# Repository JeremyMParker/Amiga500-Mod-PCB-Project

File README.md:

# Amiga500-Mod-PCB-Project
A small back panel PCB to house HDMI and several switches...
This small 4-layer PCB will take an HDMI mini cable from a Raspberry Pi RGB-to-HDMI and convert to normal size HDMI for plugging into the Amiga.
There is one small SPST push-button switch to allow menu access to the Raspberry Pi by way of a 2-pin 100mil spaced header.
A miniture DPDT switch is wired to a 4-pin 100mil header to allow the Amiga-Kit DF0/DF1 select switch cable to plug right in.
A miniture 3PDT switch is wired to a 4-pin 100mil header to allow access to the Amiga Audio Filter Mod as described in my YouTube video.
The Audio Filter control either lets the Amiga control the output low-pass filters, or overrides the Amiga and forces the filters to be enabled/disabled.
The PCB is just barely wide enough to fit in the blank space on the left side of the A500 when looking at the back.
This is my first GitHub repository, so please be patient with me!

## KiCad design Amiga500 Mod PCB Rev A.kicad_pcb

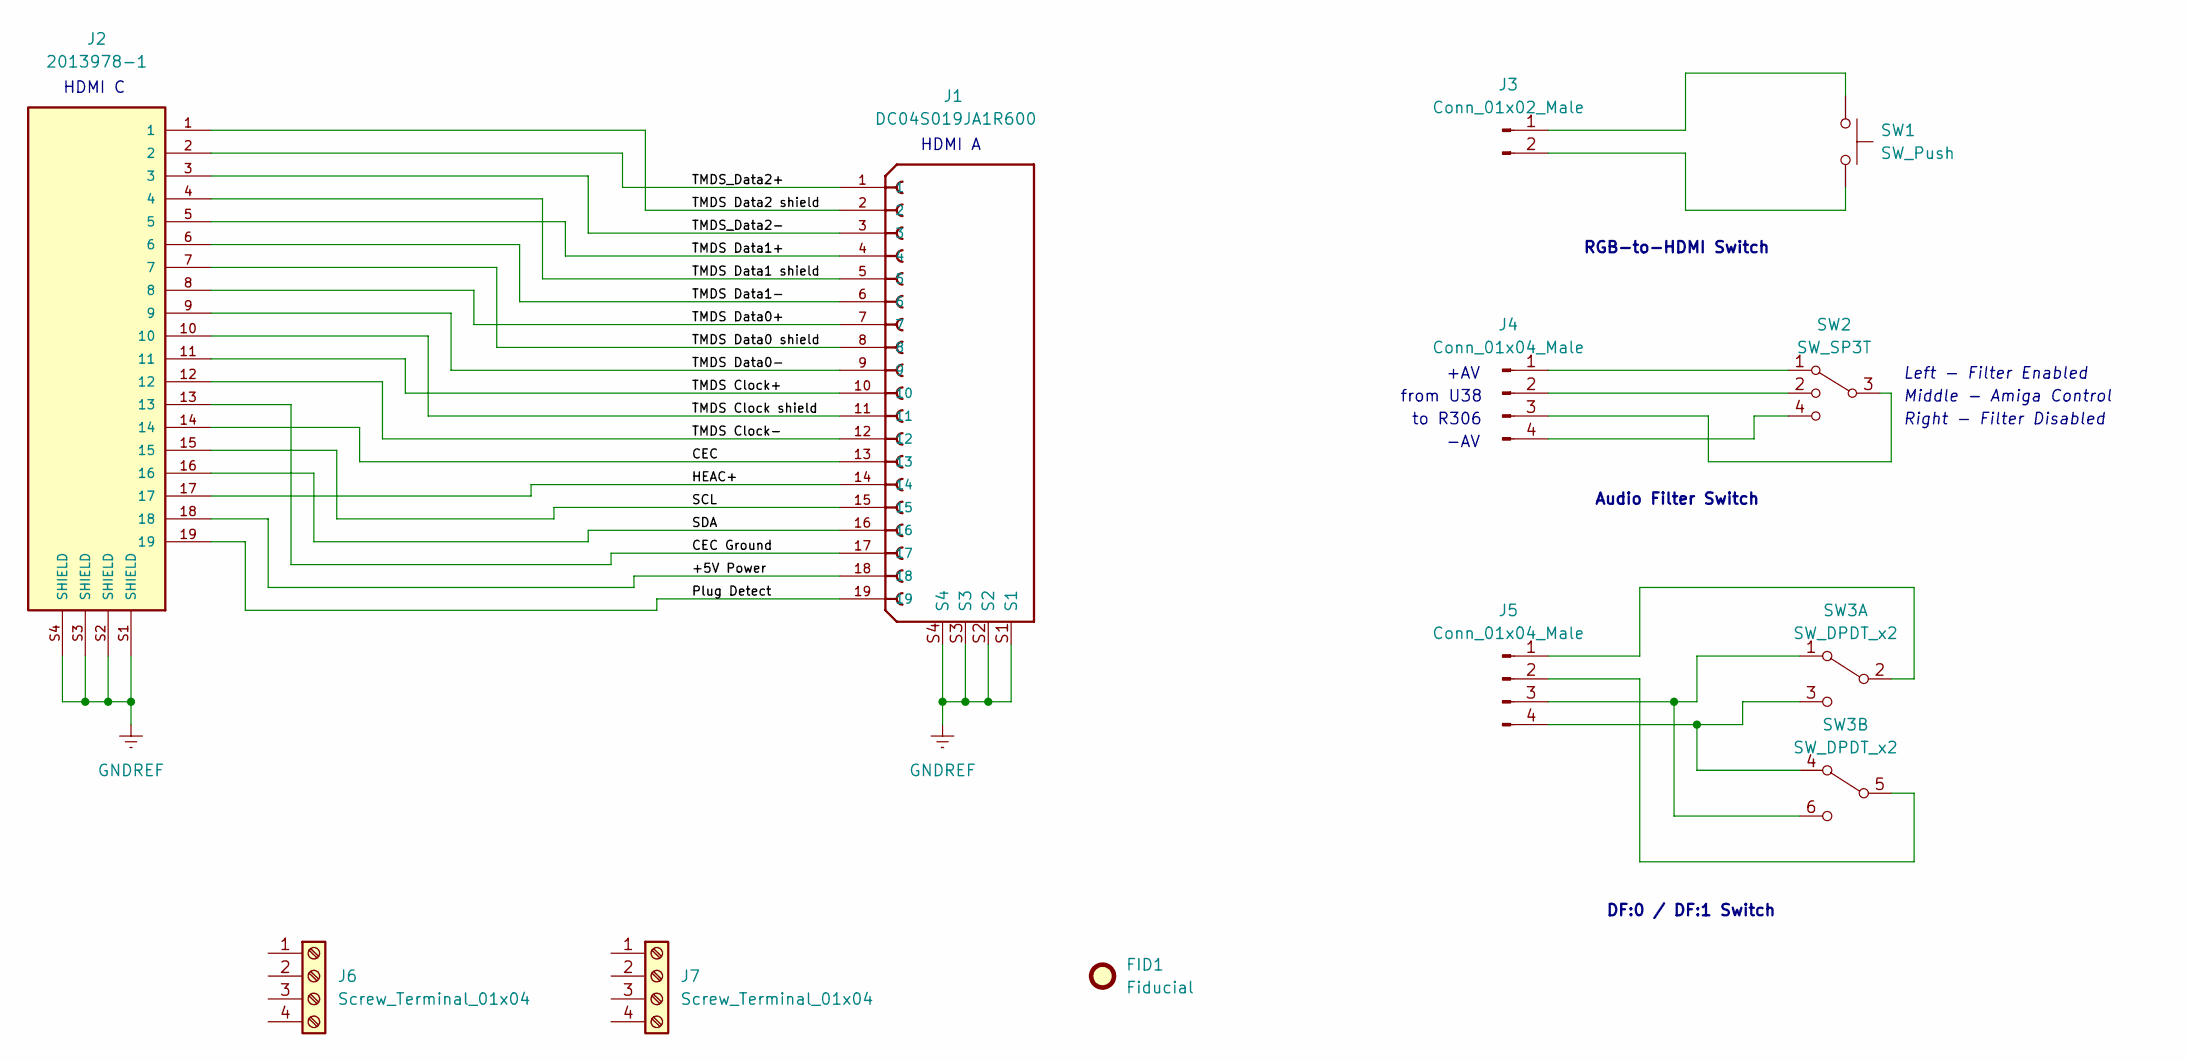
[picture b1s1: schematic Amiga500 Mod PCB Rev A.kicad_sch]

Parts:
FID1: Fiducial; Fiducial_0.5mm_Mask1.5mm
J1: DC04S019JA1R600; JAE_DC04S019JA1R600; PARTREV 1
J2: 2013978-1; TE_2013978-1; PARTREV B1
J3: Conn_01x02_Male; PinHeader_1x02_P2.54mm_Vertical
J4, J5: Conn_01x04_Male; PinHeader_1x04_P2.54mm_Vertical
J6, J7: Screw_Terminal_01x04; Keystone 4-40 screw terminal
SW1: SW_Push; SPST 800BWSP9SM6RE
SW2: SW_SP3T; SP3T CL-SB-13B-11T
SW3: SW_DPDT_x2; DPDT CL-SB-22B-12T

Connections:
/+5V Power: J1.18, J2.18
/CEC: J1.13, J2.14
/CEC Ground: J1.17, J2.13
/HEAC+: J1.14, J2.17
/Plug Detect: J1.19, J2.19
/SCL: J1.15, J2.15
/SDA: J1.16, J2.16
/TMDS Clock shield: J1.11, J2.10
/TMDS Clock+: J1.10, J2.11
/TMDS Clock-: J1.12, J2.12
/TMDS Data0 shield: J1.8, J2.7
/TMDS Data0+: J1.7, J2.8
/TMDS Data0-: J1.9, J2.9
/TMDS Data1 shield: J1.5, J2.4
/TMDS Data1+: J1.4, J2.5
/TMDS Data1-: J1.6, J2.6
/TMDS Data2 shield: J1.2, J2.1
/TMDS_Data2+: J1.1, J2.2
/TMDS_Data2-: J1.3, J2.3
GNDREF: J1.S1, J1.S2, J1.S3, J1.S4, J2.S1 (SHIELD), J2.S2 (SHIELD), J2.S3 (SHIELD), J2.S4 (SHIELD)
unnamed: J3.1, SW1.1
unnamed: J3.2, SW1.2
unnamed: J4.1, SW2.1
unnamed: J4.2, SW2.2
unnamed: J4.3, SW2.3
unnamed: J4.4, SW2.4
unnamed: J5.1, SW3.2 (B)
unnamed: J5.2, SW3.5 (B)
unnamed: J5.3, SW3.1 (A), SW3.6 (C)
unnamed: J5.4, SW3.3 (C), SW3.4 (A)

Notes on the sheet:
HDMI C
from U38
to R306
Left - Filter Enabled
RGB-to-HDMI Switch
Right - Filter Disabled
DF:0 / DF:1 Switch
Middle - Amiga Control
+AV
HDMI A
-AV
Audio Filter Switch

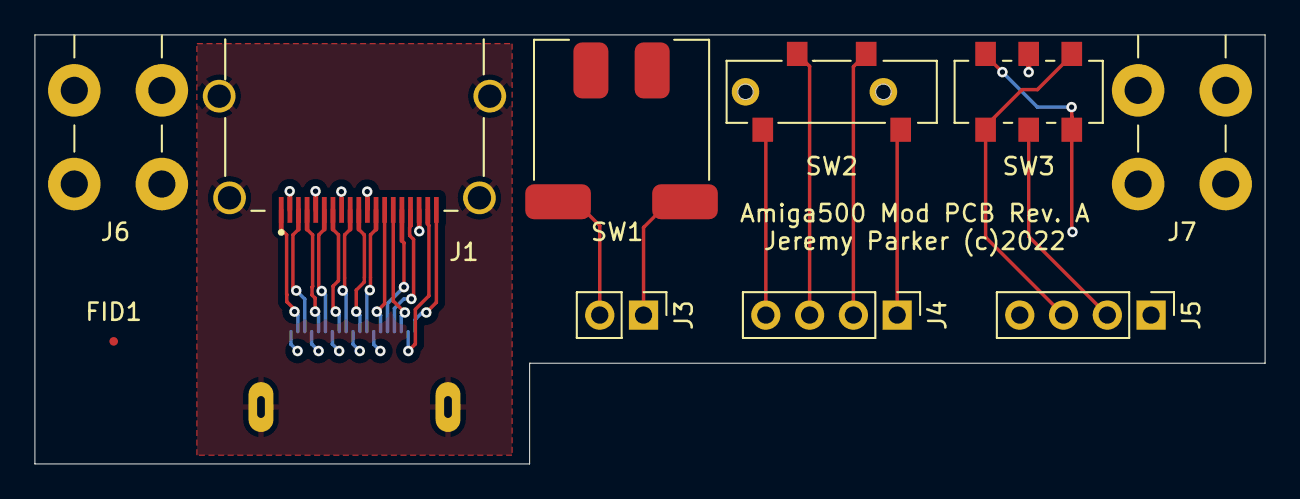
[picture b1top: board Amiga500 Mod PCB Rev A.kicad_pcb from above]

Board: 4 copper layers, 71.4 x 24.9 mm, 11 parts (1 on the bottom side), 30 nets.

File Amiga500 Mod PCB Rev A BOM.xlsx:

Item | Qty | Reference(s) | Value | LibPart | Footprint | MANUFACTURER | Digi-Key Description | Digi-Key Order #
1.0 | 1.0 | J1 | DC04S019JA1R600 | JP Symbol Library:DC04S019JA1R600_2 | SnapEDA Library:JAE_DC04S019JA1R600 | JAE | RECEPT, HDMI 2.1, 48GBPS BANDWID | 670-3154-1-ND
2.0 | 1.0 | J2 | 2013978-1 | 2013978-1:2013978-1 | SnapEDA Library:TE_2013978-1 | TE Connectivity | CONN RCPT MINI HDMI 19POS SMD RA | A107963CT-ND
3.0 | 1.0 | J3 | Conn_01x02_Male | Connector:Conn_01x02_Male | Connector_PinHeader_2.54mm:PinHeader_1x02_P2.54mm_Vertical | Hirose | CONN HEADER VERT 2POS 2.54MM | H123034-ND
4.0 | 2.0 | J4, J5 | Conn_01x04_Male | Connector:Conn_01x04_Male | Connector_PinHeader_2.54mm:PinHeader_1x04_P2.54mm_Vertical | Hirose | CONN HEADER VERT 4POS 2.54MM | H123038-ND
5.0 | 2.0 | J6, J7 | Screw_Terminal_01x04 | Connector:Screw_Terminal_01x04 | JP Library:Keystone 4-40 screw terminal | Keystone | TERM SCREW 4-40 4 PIN PCB RA | 36-7774-ND
6.0 | 1.0 | SW1 | SW_Push | Switch:SW_Push | JP Library:SPST 800BWSP9SM6RE | E-Switch | SWITCH PUSH SPST-NO 0.4VA 20V | EG2610CT-ND
7.0 | 1.0 | SW2 | SW_SP3T | Switch:SW_SP3T | JP Library:SP3T CL-SB-13B-11T | Nidec Copal Electronics | SWITCH SLIDE SP3T 200MA 12V | 563-1332-1-ND
8.0 | 1.0 | SW3 | SW_DPDT_x2 | Switch:SW_DPDT_x2 | JP Library:DPDT CL-SB-22B-12T | Nidec Copal Electronics | SWITCH SLIDE DPDT 200MA 12V | 563-1345-1-ND

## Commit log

2022-05-16 Ki-Kad files, CAM files, BOM, Schematic PDF etc.
    All the files related to the Amiga500 Mod PCB. OSH Park CAM files zipped up and ready to upload to OSH Park standard 4-layer service. BOM has Digi-Key part numbers, with generic 100mil spaced headers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

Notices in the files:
Amiga500 Mod PCB Rev A.kicad_pcb:
Jeremy Parker (c)2022
